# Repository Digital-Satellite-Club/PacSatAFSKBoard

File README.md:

# PacSatAFSKBoard
Hardware design for the PacSat AX5043 based board

This repository contains a board design for use in satellites for
packet message storing and forwarding and for general control.

It has a TMS570LS0914PGE processor for control and packet handling.
It uses 5 AX5043 chips for the radio interfaces, four receive channels
(uplinks) and one transmit channel (downlink).  Operation is full
duplex with receive on 144-148MHz and transmit on 430-440MHz.

Though it is designed for packet satellite, the design can be used for
any sort of full duplex dual band AFSK radio operation with or without
FM.  The AX5043 supports a large number of AFSK protocols (if you can
figure out how to program the AX5043).

With some filter redesign it could support a number of different
bands, too, maybe even up to 1280MHz.

The board also has MRAM storage for persistent data storage and an
RTC for timekeeping.  There's space on the board to add more things.

The board has a CAN interface and a serial interface on top of the
radio interfaces for interfacing to other boards in the system.

Output power is about 2 watts.  It has the ability to measure forward
and reflected power on the output.  It also has a sort of loopback
connector on the RF to test the receive and transmit chain.

The board is designed to be able to be used in an active/standby
configuration where you have two of the same boards and switch the RF
between the boards depending on which is active.

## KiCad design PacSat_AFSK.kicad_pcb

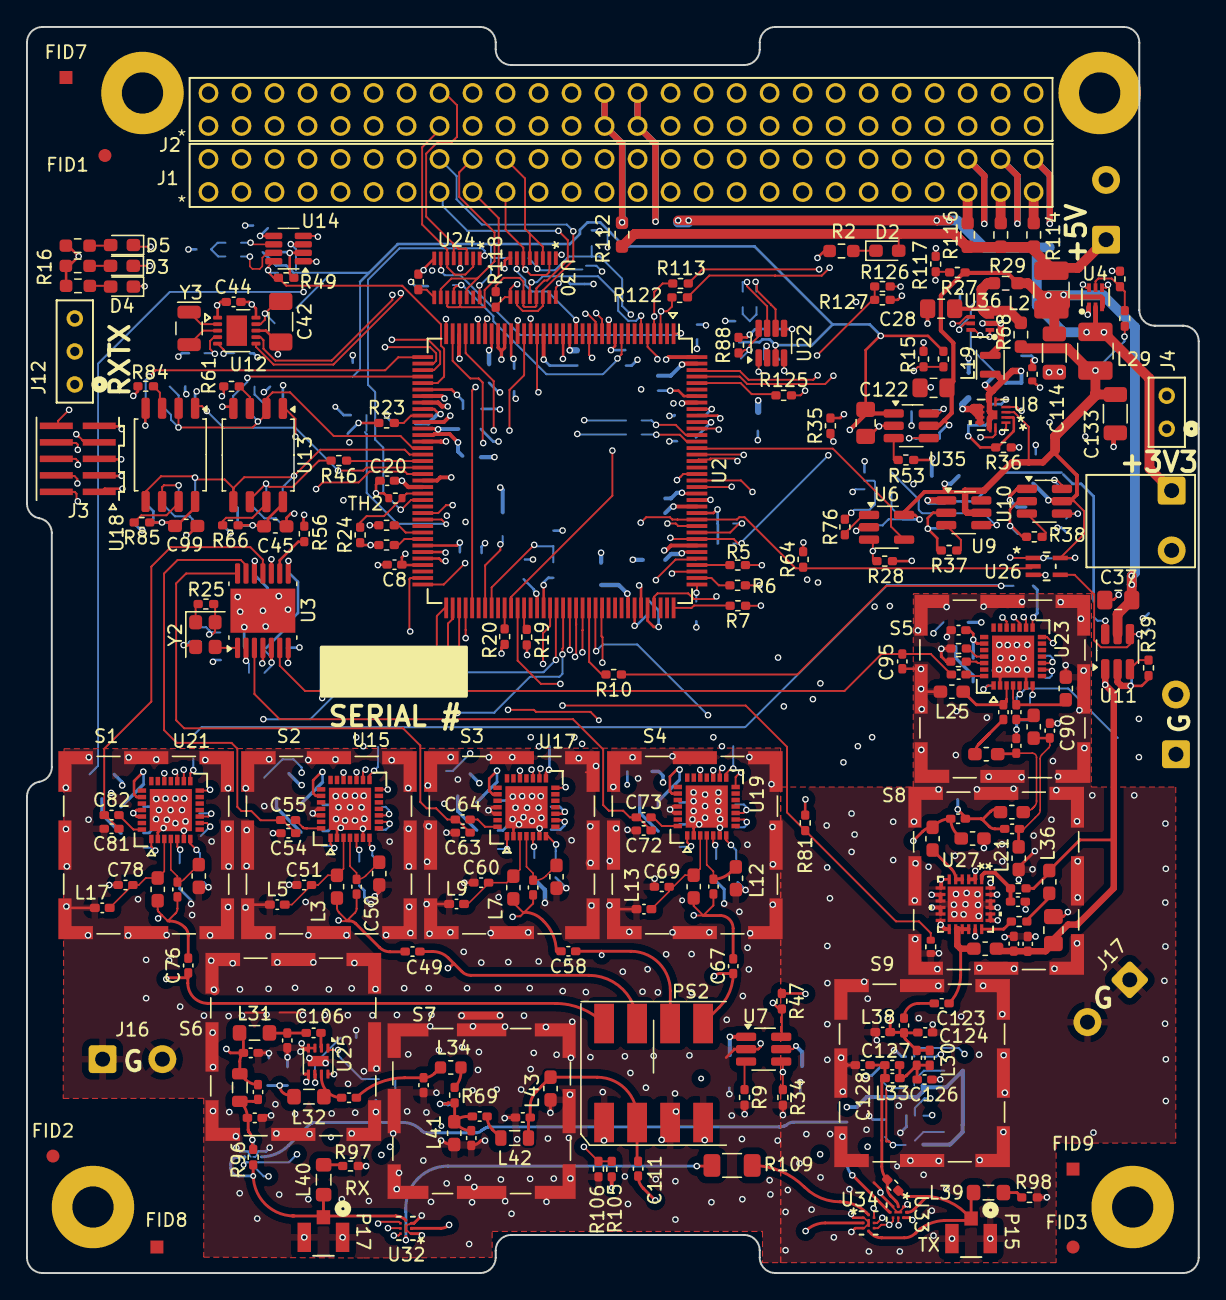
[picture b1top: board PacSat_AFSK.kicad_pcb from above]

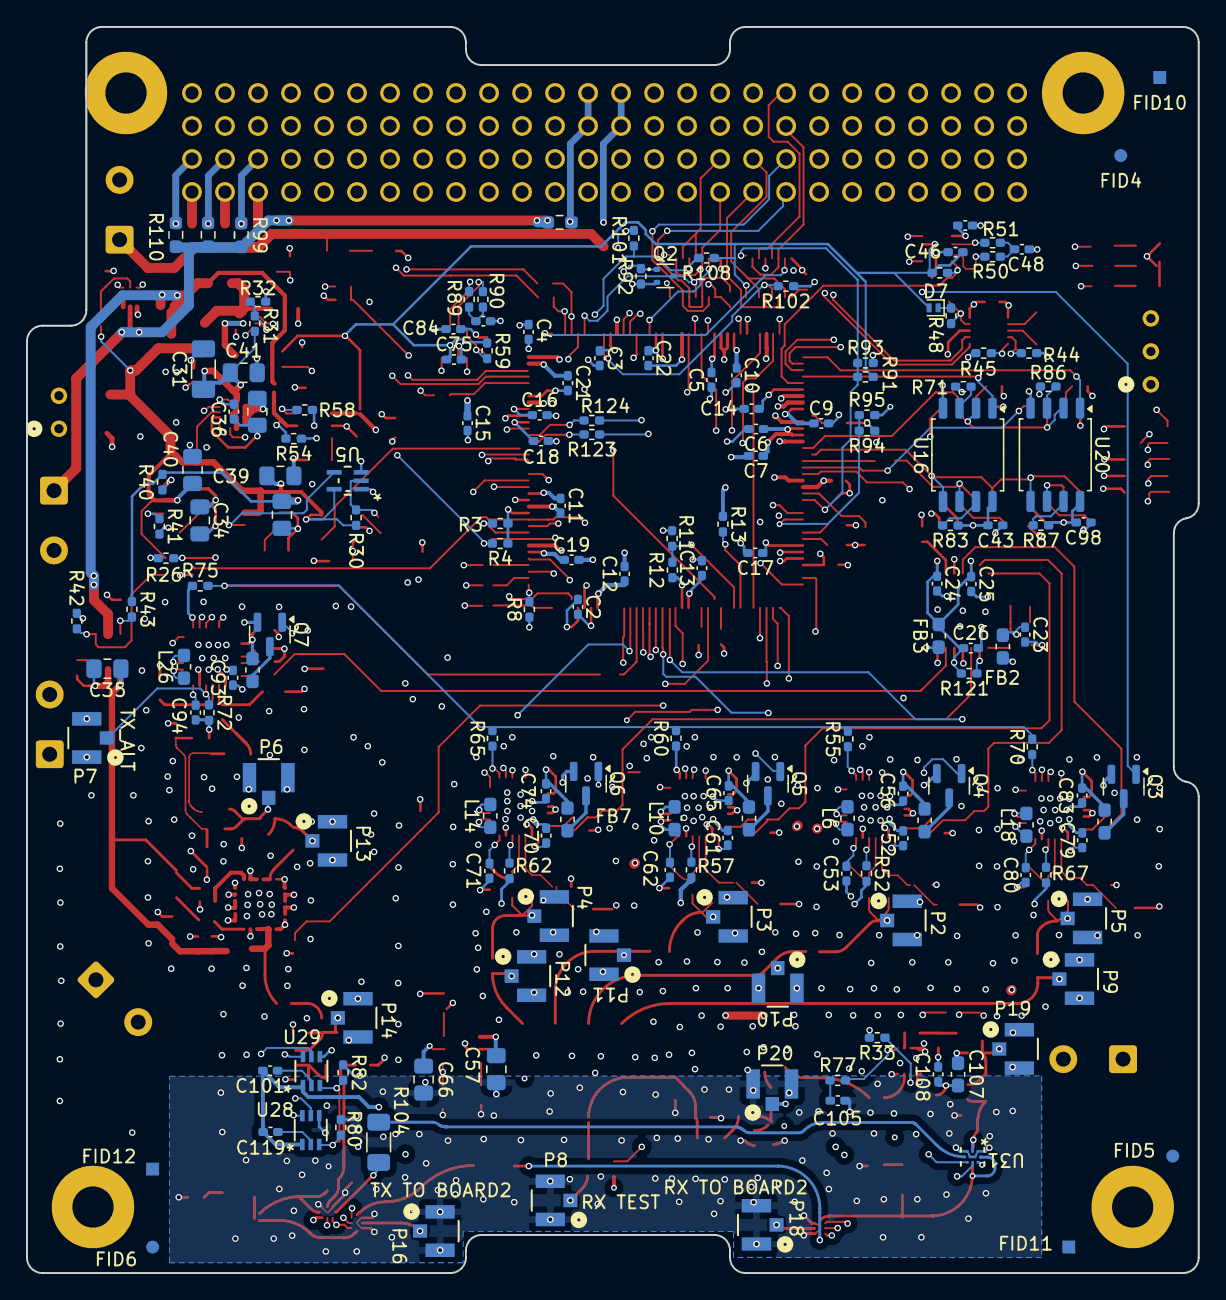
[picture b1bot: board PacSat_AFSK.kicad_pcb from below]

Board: 6 copper layers, 90.2 x 95.9 mm, 405 parts (168 on the bottom side), 283 nets.

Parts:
C2, C3, C4, C5, C6, C7, C8, C9, C10, C11, C12, C13, C14, C15, C16, C17, C18, C19, C20, C21, C22, C23, C24, C25, C26, C43, C44, C46, C47, C75, C84, C98: 100nF; C_0402_1005Metric_Pad0.74x0.62mm_HandSolder
C28: 4.7uF; C_0805_2012Metric_Pad1.18x1.45mm_HandSolder
C31: 22uF; C_1206_3216Metric_Pad1.33x1.80mm_HandSolder
C33, C34, C35, C37, C38, C39, C40, C41, C57, C66, C121, C122: 1uF; C_0805_2012Metric_Pad1.18x1.45mm_HandSolder
C36, C48, C120: 4.7nF; C_0402_1005Metric_Pad0.74x0.62mm_HandSolder
C42: 47uF 10V; C_1206_3216Metric_Pad1.33x1.80mm_HandSolder
C45, C99, C107: 1uF; C_0603_1608Metric_Pad1.08x0.95mm_HandSolder
C49, C58, C67, C76, C105, C108, C113, C115: 100pF; C_0402_1005Metric_Pad0.74x0.62mm_HandSolder
C50, C51, C59, C60, C68, C69, C77, C78: 15pF 1%; C_0402_1005Metric_Pad0.74x0.62mm_HandSolder
C52, C53, C56, C61, C62, C65, C70, C71, C74, C79, C80, C83, C93, C94, C97: 10nF; C_0402_1005Metric_Pad0.74x0.62mm_HandSolder
C54, C63, C72, C81, C95: 6.8pF; C_0402_1005Metric_Pad0.74x0.62mm_HandSolder
C55, C64, C73, C82, C96: 10pF; C_0402_1005Metric_Pad0.74x0.62mm_HandSolder
C88: 5.1pF ±.1; C_0402_1005Metric_Pad0.74x0.62mm_HandSolder
C89, C110: 11pF 1%; C_0402_1005Metric_Pad0.74x0.62mm_HandSolder
C90: 5.6pF ±.1; C_0402_1005Metric_Pad0.74x0.62mm_HandSolder
C91, C92: 4.3pF 1%; C_0402_1005Metric_Pad0.74x0.62mm_HandSolder
C100, C103: 36pF 1%; C_0402_1005Metric_Pad0.74x0.62mm_HandSolder
C101, C106, C109, C111, C112, C116, C119, C123: 1nF; C_0402_1005Metric_Pad0.74x0.62mm_HandSolder
C102: 1pF ±.05; C_0402_1005Metric_Pad0.74x0.62mm_HandSolder
C104, C131: 6.5pF ±.1; C_0402_1005Metric_Pad0.74x0.62mm_HandSolder
C114, C133: 10uF 10V; C_1206_3216Metric
C117: 110pF 1% 30V; C_0402_1005Metric_Pad0.74x0.62mm_HandSolder
C118: 10uF; C_0805_2012Metric_Pad1.18x1.45mm_HandSolder
C124: 7.3pF ±.1 30V; C_0402_1005Metric_Pad0.74x0.62mm_HandSolder
C125: 0.75pF ±.05 30V; C_0402_1005Metric_Pad0.74x0.62mm_HandSolder
C126: 12pF 1% 30V; C_0402_1005Metric_Pad0.74x0.62mm_HandSolder
C127: 2.2pF ±.05 30V; C_0402_1005Metric_Pad0.74x0.62mm_HandSolder
C128: 6.2pF ±.1 30V; C_0402_1005Metric_Pad0.74x0.62mm_HandSolder
C130, C132: 68pF 1%; C_0402_1005Metric_Pad0.74x0.62mm_HandSolder
D2: BLUE LED; LED_0603_1608Metric_Pad1.05x0.95mm_HandSolder
D3: RED LED; LED_0603_1608Metric_Pad1.05x0.95mm_HandSolder
D4: YELLOW LED; LED_0603_1608Metric_Pad1.05x0.95mm_HandSolder
D5: GREEN LED; LED_0603_1608Metric_Pad1.05x0.95mm_HandSolder
D7: RB521CS30L,315; D_SOD-882
FB2, FB3, FB4, FB5, FB6, FB7, FB8: 1KΩ@100MHz; L_0603_1608Metric_Pad1.05x0.95mm_HandSolder
FID1, FID2, FID3, FID4, FID5, FID6: Fiducial (round); Fiducial_1mm_Mask2mm
FID7, FID8, FID9, FID10, FID11, FID12: Fiducial (square); Fiducial_Square_1mm_Mask2mm
H2, H3, H4, H5: CUBESAT_MOUNT_HOLE
J1, J2: ESQ-126-39-G-D; CONN_ESQ-126-39-G-D_SAI
J3: FTSH-105-01-L-DV-K
J4: TS-102-G-A; CON2_1X2_TU_HTS_SAI
J8, J11, J14, J16, J17: Conn_01x02_Pin; SolderWire-0.5sqmm_1x02_P4.6mm_D0.9mm_OD2.1mm
J12: TS-103-G-A; CON3_1X3_TU_HTS_SAI
L2, L29: 3.3uH; L_1210_3225Metric_Pad1.42x2.65mm_HandSolder
L3, L4, L7, L8, L11, L12, L15, L16: 78nH 2%; L_0603_1608Metric_Pad1.05x0.95mm_HandSolder
L5, L9, L13, L17: 1nH; L_0402_1005Metric_Pad0.77x0.64mm_HandSolder
L6, L10, L14, L18, L26: 0; L_0603_1608Metric_Pad1.05x0.95mm_HandSolder
L19: 1uH; L_Murata_DFE201610P
L20, L21: 27nH 2%; L_0603_1608Metric_Pad1.05x0.95mm_HandSolder
L22, L23: 43nH 2%; L_0603_1608Metric_Pad1.05x0.95mm_HandSolder
L24, L25: 100nH; L_0603_1608Metric_Pad1.05x0.95mm_HandSolder
L27: 3.3nH 2%; L_0603_1608Metric_Pad1.05x0.95mm_HandSolder
L28: 43nH 2%; L_0805_2012Metric
L30: 22nH 2%; L_0402_1005Metric_Pad0.77x0.64mm_HandSolder
L31: 91nH 2%; L_0805_2012Metric_Pad1.05x1.20mm_HandSolder
L32: 180nH 2%; L_0805_2012Metric_Pad1.05x1.20mm_HandSolder
L33: 18nH 2%; L_0402_1005Metric_Pad0.77x0.64mm_HandSolder
L34: 47nH 2%; L_0603_1608Metric
L35: 11nH 2%; L_0603_1608Metric_Pad1.05x0.95mm_HandSolder
L36: 68nH; L_0603_1608Metric_Pad1.05x0.95mm_HandSolder
L37: 36nH I>1A; L_0603_1608Metric_Pad1.05x0.95mm_HandSolder
L38: 6.9nH 2%; L_0402_1005Metric_Pad0.77x0.64mm_HandSolder
L39, L40: 470nH; L_0805_2012Metric_Pad1.05x1.20mm_HandSolder
L41, L43: 18nH 2%; L_0603_1608Metric_Pad1.05x0.95mm_HandSolder
L42: 180nH 2%; L_0805_2012Metric
P2, P3, P4, P5, P6, P7, P8, P9, P10, P11, P12, P13, P14, P15, P16, P17, P18, P19, P20: CONUFL001-SMD-T; CONN1_CONUFL_TEC
PS2: AD4PS-1+; CJ725
Q2: BSS138; SOT-523
Q3, Q4, Q5, Q6, Q7: DMP2037U-7; SOT-23
R2: 2.4KΩ; R_0603_1608Metric_Pad0.98x0.95mm_HandSolder
R3, R4, R8, R11, R12, R13, R14, R15, R23, R25, R26, R27, R28, R30, R33, R34, R40, R41, R42, R43, R47, R49, R54, R58, R59, R61, R63, R64, R66, R71, R83, R84, R85, R86, R87, R88, R91, R92, R93, R94, R95, R97, R98, R101, R103, R105, R106, R108, R117, R121: 10KΩ; R_0402_1005Metric_Pad0.72x0.64mm_HandSolder
R5, R6, R7: 22Ω; R_0402_1005Metric_Pad0.72x0.64mm_HandSolder
R9, R38, R53: 143KΩ 1%; R_0402_1005Metric_Pad0.72x0.64mm_HandSolder
R10, R46, R56: 33Ω; R_0402_1005Metric_Pad0.72x0.64mm_HandSolder
R16, R17, R18: 3KΩ; R_0603_1608Metric_Pad0.98x0.95mm_HandSolder
R19, R20, R21, R22: 1KΩ; R_0402_1005Metric_Pad0.72x0.64mm_HandSolder
R24, R35, R81: 10KΩ 1%; R_0402_1005Metric_Pad0.72x0.64mm_HandSolder
R29, R68, R99, R100, R110, R111, R112, R114, R115, R116: 0Ω; R_0603_1608Metric_Pad0.98x0.95mm_HandSolder
R31, R32: 68KΩ 1%; R_0402_1005Metric_Pad0.72x0.64mm_HandSolder
R36: 47KΩ 1%; R_0402_1005Metric_Pad0.72x0.64mm_HandSolder
R37, R39: 45.3KΩ 1%; R_0402_1005Metric_Pad0.72x0.64mm_HandSolder
R44, R45, R48: 4.7KΩ; R_0402_1005Metric_Pad0.72x0.64mm_HandSolder
R50, R51, R89, R90: 61.9Ω; R_0402_1005Metric_Pad0.72x0.64mm_HandSolder
R52, R57, R62, R67, R72, R80, R82: 50Ω; R_0402_1005Metric_Pad0.72x0.64mm_HandSolder
R55, R60, R65, R70, R75: 470Ω; R_0402_1005Metric_Pad0.72x0.64mm_HandSolder
R69, R73, R74, R76, R96, R107, R113, R118, R122, R123, R124, R125, R126, R127: 0Ω; R_0402_1005Metric_Pad0.72x0.64mm_HandSolder
R77: 3.32KΩ 1%; R_0402_1005Metric_Pad0.72x0.64mm_HandSolder
R78: 280Ω; R_0402_1005Metric_Pad0.72x0.64mm_HandSolder
R79: 240Ω; R_0402_1005Metric_Pad0.72x0.64mm_HandSolder
R102: 1MΩ; R_0402_1005Metric_Pad0.72x0.64mm_HandSolder
R104, R109: 50Ω >=2W; R_1206_3216Metric_Pad1.30x1.75mm_HandSolder
R119: 88.7KΩ 1%; R_0402_1005Metric_Pad0.72x0.64mm_HandSolder
R120: 19.6KΩ 1%; R_0402_1005Metric_Pad0.72x0.64mm_HandSolder
S1, S2, S3, S4, S5, S6, S7, S8, S9: 2118714-2; TE_2118714-2
TH2, TH3, TH4: NTCG103JF103FTDS 10KΩ@25C; R_0402_1005Metric
U2: TMS5700914APGEQQ1; TQFP-144_20x20mm_Pitch0.5mm
U3: LMK1C1106A; Texas_HTSSOP-14-1EP_4.4x5mm_P0.65mm_EP3.4x5mm_Mask3.155x3.2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
U4, U36: TPS62A02AQDRLRQ1; DRL0006A-MFG
U5: SN74AHC1G09QDCKRQ1; DCK5
U6: STWD100NYWY3F; SOT-23-5_HandSoldering
U7, U9, U10, U11, U35: MAX4995AAUT+T; SOT-23-6_Handsoldering
U8: MP5073GG-P; QFN-12_MP5073_MNP
U12: MAX31331TETB+; TDFN-10-1EP_3x3mm_P0.5mm_EP0.9x2mm
U13, U16, U18, U20: AS1016204-0108X0PSAY; SOIC-8_5.3x5.3mm_P1.27mm
U14, U22: TCAN1044ADDFRQ1; TSOT-23-8
U15, U17, U19, U21, U23: AX5043; QFN28
U24, U30: SN3257QDYYRQ1; DYY0016A
U25: QPL9547; DFN-8-1EP_2x2mm_P0.5mm_EP0.8x1.6mm
U26: SN74AHC1G02QDCKRQ1; DCK5
U27: TQP7M9106; QFN24_TQP7M9104_QOR
U28, U29: ADL5501AKSZ-R7; KS-6_ADI
U31, U32, U33, U34: QPC1022TR7; QPC1022_QOR
Y2: O 16,0-JT22CT-A-P-3,3-LF; Oscillator_SMD_SiT_PQFN-4Pin_2.5x2.0mm
Y3: 32.768kHz; Crystal_SMD_EuroQuartz_EQ161-2Pin_3.2x1.5mm

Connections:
3.3V_IN: J14.1, L29.1, R99.2, R100.2, R110.2, R111.2, U4.2 (SW)
5V_IN: D2.2 (A), J11.1, L2.2, R112.1, R114.1, R115.1, R116.1
+1.2V: C6.1, C7.1, C9.1, C10.1, C11.1, C12.1, C13.1, C15.1, C19.1, C20.1, C21.1, C22.1, C38.1, R13.1, U2.17 (VCC), U2.29 (VCC), U2.45 (VCC), U2.48 (VCC), U2.49 (VCC), U2.57 (VCC), U2.87 (VCC), U2.101 (VCC), U2.114 (VCC), U2.123 (VCC), U2.137 (VCC), U2.143 (VCC), U8.7 (NC), U8.8 (NC), U8.9 (VOUT), U8.10 (NC)
+3.3V: C2.1, C3.1, C4.1, C5.1, C8.1, C14.1, C16.1, C17.1, C18.1, C33.1, C43.1, C44.1, C45.1, C47.1, C84.1, C98.1, C99.1, C101.2, C119.2, FB2.1, FB3.1, J3.1, R3.1, R4.1, R8.1, R11.1, R16.1, R17.1, R18.1, R21.1, R23.1, R24.1, R35.1, R40.1, R43.1, R47.1, R58.1, R61.2, R66.1, R71.2, R81.1, R83.1, R84.2, R85.1, R86.2, R87.1, R94.1, R102.1, U2.10 (VCCIO), U2.26 (VCCIO), U2.42 (VCCIO), U2.66 (ADREFHI), U2.69 (VCCAD), U2.104 (VCCIO), U2.120 (VCCIO), U2.134 (VCCP), U2.136 (VCCIO), U9.1 (OUT), U12.10 (VCC), U13.8 (VCC), U14.5 (NC/VIO), U16.8 (VCC), U18.8 (VCC), U20.8 (VCC), U22.5 (NC/VIO), U28.1 (VPOS), U29.1 (VPOS)
+5V: C37.1, C114.1, C122.1, L2.1, R27.2, R29.1, R54.2, U4.3 (VIN), U11.5 (IN), U35.5 (IN)
+5VAL: C46.1, C66.1, C75.1, C121.1, D7.2 (A), R14.1, R59.1, R63.1, R91.1, R105.1, R108.1, U7.5 (IN), U14.3 (VCC), U22.3 (VCC), U24.16 (VDD), U30.16 (VDD), U31.7 (VDD), U32.7 (VDD), U33.7 (VDD), U34.7 (VDD), U35.1 (OUT)
/AX5043/RX_1_ax5043/RXANT_N: C77.1, L16.2, U21.4 (ANTN)
/AX5043/RX_1_ax5043/RXANT_P: C78.2, L15.2, L17.2, U21.3 (ANTP)
/AX5043/RX_2_ax5043/RX2ANT_N: C50.1, L4.2, U15.4 (ANTN)
/AX5043/RX_2_ax5043/RX2ANT_P: C51.2, L3.2, L5.2, U15.3 (ANTP)
/AX5043/RX_3_ax5043/RX3_N: C59.1, L8.2, U17.4 (ANTN)
/AX5043/RX_3_ax5043/RX3_P: C60.2, L7.2, L9.2, U17.3 (ANTP)
/AX5043/RX_4_ax5043/RX4ANT_N: C68.1, L12.2, U19.4 (ANTN)
/AX5043/RX_4_ax5043/RX4ANT_P: C69.2, L11.2, L13.2, U19.3 (ANTP)
/AX5043/TX_ax5043/TXANT_N: C92.1, L24.2, U23.4 (ANTN)
/AX5043/TX_ax5043/TXANT_P: C91.1, L25.2, U23.3 (ANTP)
/AX5043/TX_ax5043/TXa_N: C92.2, L23.2
/AX5043/TX_ax5043/TXa_P: C91.2, L22.2
/AX5043/TX_ax5043/TXb_N: C88.1, C90.1, L21.1, L23.1
/AX5043/TX_ax5043/TXb_P: C89.1, L20.2, L22.1
/PC104_IO/3V3_S1: J1.48, R99.1
/PC104_IO/3V3_S2: J1.50, R100.1
/PC104_IO/3V3_S3: J1.52, R110.1
/PC104_IO/3V3_p: J2.27, J2.28, R111.1
/PC104_IO/5V_S1: J1.47, R116.2
/PC104_IO/5V_S2: J1.49, R115.2
/PC104_IO/5V_S3: J1.51, R114.2
/PC104_IO/5V_p: J2.25, J2.26, R112.2
/PC104_IO/VBATT_p: J2.45, J2.46, R126.1
/Power/1.2V_INPUT: C28.1, R29.2, R68.2, U36.3 (VIN)
/Power/PA_POWER_ON: R42.1, U11.4 (ON), U26.4 (Y)
/Power/WATCHDOG_OUT_N: R30.2, R76.1, U5.2 (B)
/Rx_Power_Divider/S+: C111.2, C132.2, L42.1, L43.1, PS2.2 (S1)
ACTIVE1_N: J1.19, U30.2 (S1A), U30.6 (S2B), U31.5 (CTRL), U32.5 (CTRL), U33.5 (CTRL), U34.5 (CTRL)
ACTIVE2_N: J1.20, U30.3 (S1B), U30.5 (S2A)
ACTIVE_N: R101.1, R108.2, U2.133 (GIOB_1), U30.4 (D1)
AX5043 PWR EN: R41.1, U2.141 (N2HET1_20), U10.4 (ON)
AX5043_3V3: C34.1, Q3.2 (S), Q4.2 (S), Q5.2 (S), Q6.2 (S), Q7.2 (S), U10.1 (OUT)
AX5043_CLK: R10.1, R55.2, R60.2, R65.2, R70.2, R75.2
AX5043_EN_RX1_N: Q3.1 (G), U2.36 (N2HET1_4)
AX5043_EN_RX2_N: Q4.1 (G), U2.35 (N2HET1_9)
AX5043_EN_RX3_N: Q5.1 (G), U2.33 (N2HET1_7)
AX5043_EN_RX4_N: Q6.1 (G), U2.24 (N2HET1_3)
AX5043_EN_TX_N: Q7.1 (G), U2.89 (CAN1TX)
AX5043_IRQ_RX1: U2.5 (GIOA_1), U21.19 (IRQ)
AX5043_IRQ_RX2: U2.126 (GOIB_0), U15.19 (IRQ)
AX5043_IRQ_RX3: U2.22 (GIOA_7), U17.19 (IRQ)
AX5043_IRQ_RX4: U2.14 (GIOA_5), U19.19 (IRQ)
AX5043_IRQ_TX: U2.142 (GIOB_2), U23.19 (IRQ)
AX5043_MISO: U2.94 (MIBSPI1SOMI), U15.16 (MISO), U17.16 (MISO), U19.16 (MISO), U21.16 (MISO), U23.16 (MISO)
AX5043_MOSI: U2.93 (MIBSPI1SIMO), U15.17 (MOSI), U17.17 (MOSI), U19.17 (MOSI), U21.17 (MOSI), U23.17 (MOSI)
AX5043_SEL1_N: U2.90 (CAN1RX), U21.14 (SEL)
AX5043_SEL2_N: U2.91 (N2HET1_24), U15.14 (SEL)
AX5043_SEL3_N: U2.92 (N2HET1_26), U17.14 (SEL)
AX5043_SEL4_N: U2.96 (MIBSPI1NENA), U19.14 (SEL)
AX5043_SEL_TX_N: U2.97 (MIBSPI5NENA), U23.14 (SEL)
BOARD1_RF_BYPASS: R104.2, U31.4 (RF1)
BOARD2_RF_BYPASS: R109.2, U32.8 (RF2)
BOARD_NUM: R91.2, R93.1, U2.59 (AD1IN_17), U24.1 (SEL), U30.1 (SEL)
CANA+: J1.23, R50.1, U14.7 (CA_NH)
CANA-: J1.24, R51.2, U14.6 (CA_NL)
CANB+: J1.33, R89.1, U22.7 (CA_NH)
CANB-: J1.34, R90.2, U22.6 (CA_NL)
CAN_A_EN_N: R49.1, R63.2, U2.41 (N2HET1_15), U14.8 (STB)
CAN_A_RX: U2.12 (CAN3RX), U14.4 (RX_D)
CAN_A_TX: U2.13 (CAN3TX), U14.1 (TXD)
CAN_B_EN_N: R59.2, R88.1, U2.105 (MIBSPI1NCS_0), U22.8 (STB)
CAN_B_RX: U2.129 (CAN2RX), U22.4 (RX_D)
CAN_B_TX: U2.128 (CAN2TX), U22.1 (TXD)
Clock_CPU: R56.2, U2.18 (OSCIN)
Clock_RX1: C81.1, C82.1, U3.11 (Y2)
Clock_RX2: C54.1, C55.1, U3.13 (Y3)
Clock_RX3: C63.1, C64.1, U3.14 (Y1)
Clock_RX4: C72.1, C73.1, U3.3 (YO)
Clock_TX: C95.2, C96.1, U3.6 (Y4)
EXTERN_CONTROL: R94.2, R95.1, U2.62 (AD1IN_18)
FAULT1_N: J2.15, U24.2 (S1A), U24.6 (S2B)
FAULT2_N: J2.16, U24.3 (S1B), U24.5 (S2A)
FAULT_N: R3.2, U2.117 (nERROR), U24.4 (D1)
FEED_WATCHDOG: U2.130 (MIBSPI1NCS_1), U6.4 (WDI)
FWD_PWR: U2.74 (AD1IN_3), U29.6 (VRMS)
GND: C2.2, C3.2, C4.2, C5.2, C6.2, C7.2, C8.2, C9.2, C10.2, C11.2, C12.2, C13.2, C14.2, C15.2, C16.2, C17.2, C18.2, C19.2, C20.2, C21.2, C22.2, C23.2, C24.2, C25.2, C26.2, C28.2, C31.2, C33.2, C34.2, C35.2, C36.2, C37.2, C38.2, C39.1, C40.2, C41.2, C42.2, C43.2, C44.2, C45.2, C46.2, C47.2, C48.2, C51.1, C52.2, C53.2, C54.2, C56.2, C57.2, C60.1, C61.2, C62.2, C63.2, C65.2, C66.2, C69.1, C70.2, C71.2, C72.2, C74.2, C75.2, C78.1, C79.2, C80.1, C81.2, C83.2, C84.2, C89.2, C90.2, C93.2, C94.2, C95.1, C97.2, C98.2, C99.2, C100.1, C103.1, C104.2, C105.2, C107.1, C108.1, C110.1, C113.2, C114.2, C115.2, C116.2, C118.2, C120.2, C121.2, C122.2, C124.1, C126.1, C128.1, C130.1, C132.1, C133.2, H2.1, H3.1, H4.1, H5.1, J2.29, J2.30, J2.32, J3.3, J3.5, J3.9, J8.1, J8.2, J11.2, J12.3 (GND), J14.2, J16.1, J16.2, J17.1, J17.2, L4.1, L5.1, L8.1, L9.1, L12.1, L13.1, L16.1, L17.1, L21.2, L24.1, L25.1, L27.1, L38.1, L41.2, L43.2, P2.2, P2.3, P3.2, P3.3, P4.2, P4.3, P5.2, P5.3, P6.2, P6.3, P7.2, P7.3, P8.2, P8.3, P9.2, P9.3, P10.2, P10.3, P11.2, P11.3, P12.2, P12.3, P13.2, P13.3, P14.2, P14.3, P15.2, P15.3, P16.2, P16.3, P17.2, P17.3, P18.2, P18.3, P19.2, P19.3, P20.2, P20.3, PS2.1 (GND), PS2.3 (GND), PS2.4 (GND), Q2.2 (S), R2.2, R9.2, R12.2, R15.2, R19.1, R20.1, R22.1, R28.2, R32.1, R33.2, R34.2, R36.2, R37.2, R38.2, R39.2, R41.2, R42.2, R44.1, R45.1, R49.2, R52.2, R53.2, R57.2, R62.2, R64.2, R67.2, R72.2, R73.2, R74.2, R80.2, R82.2, R88.2, R92.2, R93.2, R95.2, R97.2, R98.2, R101.2, R103.2, R106.2, R117.1, R120.1, R127.2, S1.SH1 (SHIELD), S1.SH2 (SHIELD__1), S1.SH3 (SHIELD__2), S1.SH4 (SHIELD__3), S1.SH5 (SHIELD__4), S1.SH6 (SHIELD__5), S1.SH7 (SHIELD__6), S1.SH8 (SHIELD__7), S2.SH1 (SHIELD), S2.SH2 (SHIELD__1), S2.SH3 (SHIELD__2), S2.SH4 (SHIELD__3), S2.SH5 (SHIELD__4), S2.SH6 (SHIELD__5), S2.SH7 (SHIELD__6), S2.SH8 (SHIELD__7), S3.SH1 (SHIELD), S3.SH2 (SHIELD__1), S3.SH3 (SHIELD__2), S3.SH4 (SHIELD__3), S3.SH5 (SHIELD__4), S3.SH6 (SHIELD__5), S3.SH7 (SHIELD__6), S3.SH8 (SHIELD__7), S4.SH1 (SHIELD), S4.SH2 (SHIELD__1), S4.SH3 (SHIELD__2), S4.SH4 (SHIELD__3), S4.SH5 (SHIELD__4), S4.SH6 (SHIELD__5), S4.SH7 (SHIELD__6), S4.SH8 (SHIELD__7), S5.SH1 (SHIELD), S5.SH2 (SHIELD__1), S5.SH3 (SHIELD__2), S5.SH4 (SHIELD__3), S5.SH5 (SHIELD__4), S5.SH6 (SHIELD__5), S5.SH7 (SHIELD__6), S5.SH8 (SHIELD__7), S6.SH1 (SHIELD), S6.SH2 (SHIELD__1), S6.SH3 (SHIELD__2), S6.SH4 (SHIELD__3), S6.SH5 (SHIELD__4), S6.SH6 (SHIELD__5), S6.SH7 (SHIELD__6), S6.SH8 (SHIELD__7), S7.SH1 (SHIELD), S7.SH2 (SHIELD__1), S7.SH3 (SHIELD__2), S7.SH4 (SHIELD__3), S7.SH5 (SHIELD__4), S7.SH6 (SHIELD__5), S7.SH7 (SHIELD__6), S7.SH8 (SHIELD__7), S8.SH1 (SHIELD), S8.SH2 (SHIELD__1), S8.SH3 (SHIELD__2), S8.SH4 (SHIELD__3), S8.SH5 (SHIELD__4), S8.SH6 (SHIELD__5), S8.SH7 (SHIELD__6), S8.SH8 (SHIELD__7), S9.SH1 (SHIELD), S9.SH2 (SHIELD__1), S9.SH3 (SHIELD__2), S9.SH4 (SHIELD__3), S9.SH5 (SHIELD__4), S9.SH6 (SHIELD__5), S9.SH7 (SHIELD__6), S9.SH8 (SHIELD__7), TH2.2, TH3.2, TH4.2, U2.11 (VSS), U2.21 (VSS), U2.27 (VSS), U2.28 (VSS), U2.34 (TEST), U2.43 (VSS), U2.44 (VSS), U2.47 (VSS), U2.50 (VSS), U2.56 (VSS), U2.67 (ADREFLO), U2.68 (VSSAD), U2.88 (VSS), U2.102 (VSS), U2.103 (VSS), U2.115 (VSS), U2.121 (VSS), U2.122 (VSS), U2.135 (VSS), U2.138 (VSS), U2.144 (VSS), U3.4 (GND), U3.7 (GND), U3.10 (GND), U3.15 (PAD), U4.1 (GND), U5.3 (GND), U6.2 (GND), U7.2 (GND), U8.2 (GND), U9.2 (GND), U10.2 (GND), U11.2 (GND), U12.1 (GND), U12.8 (DIN), U13.4 (GND), U14.2 (GND), U15.0 (GND), U15.2 (GND), U15.6 (GND), U15.25 (GPADC1), U15.26 (GPADC2), U16.4 (GND), U17.0 (GND), U17.2 (GND), U17.6 (GND), U17.25 (GPADC1), U17.26 (GPADC2), U18.4 (GND), U19.0 (GND), U19.2 (GND), U19.6 (GND), U19.25 (GPADC1), U19.26 (GPADC2), U20.4 (GND), U21.0 (GND), U21.2 (GND), U21.6 (GND), U21.25 (GPADC1), U21.26 (GPADC2), U22.2 (GND), U23.0 (GND), U23.2 (GND), U23.6 (GND), U24.8 (GND), U25.3 (GND), U25.4 (GND), U25.5 (GND), U25.8 (GND), U25.9 (GND), U26.3 (GND), U27.2 (GND), U27.3 (GND), U27.6 (GND), U27.7 (GND), U27.8 (GND), U27.9 (GND), U27.10 (GND), U27.11 (GND), U27.12 (GND), U27.13 (GND), U27.17 (GND), U27.19 (GND), U27.20 (GND), U27.21 (GND), U27.22 (GND), U27.23 (GND), U27.24 (GND), U27.25 (RF/DC-GND), U28.4 (COMM), U29.4 (COMM), U30.8 (GND), U31.1 (GND), U31.3 (GND), U31.9 (GND), U32.1 (GND), U32.3 (GND), U32.9 (GND), U33.1 (GND), U33.3 (GND), U33.9 (GND), U34.1 (GND), U34.3 (GND), U34.9 (GND), U35.2 (GND), U36.1 (GND), Y2.2 (GND)
HW_POWER_OFF1_N: J1.15, R118.1, U30.11 (S3A), U30.13 (S4B)
HW_POWER_OFF2_N: J1.16, U30.10 (S3B), U30.14 (S4A)
HW_POWER_OFF_N: R27.1, R117.2, R118.2, U4.4 (EN), U5.1 (A), U30.9 (D3), U36.4 (EN)
I2C_SCL: R122.2, U2.3 (MIBSPI3NCS_3), U12.6 (SCL)
I2C_SDA: R113.2, U2.4 (MIBSPI3NCS_2), U12.7 (SDA)
LNA_ENABLE: R34.1, U2.31 (N2HET1_5), U7.4 (ON)
LNA_VCC: C57.1, C107.2, C108.2, L32.1, U7.1 (OUT)
MRAM_CLK: R46.1, U2.53 (MIBSPI3CLK)
MRAM_MISO: U2.51 (MIBSPI3SOMI), U13.2 (SO/IO1), U16.2 (SO/IO1), U18.2 (SO/IO1), U20.2 (SO/IO1)
MRAM_MOSI: U2.52 (MIBSPI3SIMO), U13.5 (SI/IO0), U16.5 (SI/IO0), U18.5 (SI/IO0), U20.5 (SI/IO0)
MRAM_NCS0: U2.55 (MIBSPI3NCS_0), U13.1 (CS)
MRAM_NCS1: U2.54 (MIBSPI3NENA), U18.1 (CS)
MRAM_NCS2: U2.40 (MIBSPI1NCS_2), U16.1 (CS)
MRAM_NCS3: U2.37 (MIBSPI3NCS_1), U20.1 (CS)
unnamed: C24.1, C25.1, C26.1, FB3.2, R121.1, U3.5 (Vdd), U3.8 (Vdd), U3.12 (Vdd)
unnamed: C48.1, R50.2, R51.1
unnamed: C52.1, U15.1 (VDD_ANA)
unnamed: C53.1, U15.7 (VDD_ANA)
unnamed: C61.1, U17.1 (VDD_ANA)
unnamed: C62.1, U17.7 (VDD_ANA)
unnamed: C70.1, U19.1 (VDD_ANA)
unnamed: C71.1, U19.7 (VDD_ANA)
unnamed: C79.1, U21.1 (VDD_ANA)
unnamed: C80.2, U21.7 (VDD_ANA)
unnamed: C93.1, U23.1 (VDD_ANA)
unnamed: C94.1, U23.7 (VDD_ANA)
unnamed: C104.1, C106.2, L31.1
unnamed: C105.1, R77.1
unnamed: C106.1, U25.2
unnamed: C109.1, C110.2, L34.2
unnamed: C109.2, L32.2, U25.7
unnamed: C117.2, C123.2
unnamed: C120.1, R89.2, R90.1
unnamed: C123.1, L37.1, U27.14 (RFOUT/VCC), U27.15 (RFOUT/VCC), U27.16 (RFOUT/VCC)
unnamed: C125.2, C126.2, C127.1, L30.2, L33.1
unnamed: C131.1, L42.2
unnamed: D2.1 (K), R2.1
unnamed: D3.2 (A), R16.2
unnamed: D3.1 (K), U2.25 (N2HET1_0)
unnamed: D4.2 (A), R17.2
unnamed: D4.1 (K), U2.23 (N2HET1_1)
unnamed: D5.2 (A), R18.2
unnamed: D5.1 (K), U2.30 (N2HET1_2)
unnamed: D7.1 (K), R48.2
unnamed: J1.41, R113.1
unnamed: J1.43, R122.1
unnamed: J2.21, R123.1
unnamed: J2.22, R124.2
unnamed: J2.50, R125.2
unnamed: J3.2, R7.1
unnamed: J3.4, R5.1
unnamed: J3.6, U2.111 (TDO)
unnamed: J3.7, U2.113 (RTCK)
unnamed: J3.8, R6.1
unnamed: J12.1 (RX), U2.38 (N2HET1_6)
unnamed: J12.2 (TX), U2.39 (N2HET1_13)
unnamed: L34.1, R69.1
unnamed: L35.2, U27.4 (RFIN), U27.5 (RFIN)
unnamed: L36.1, R79.1
unnamed: L39.2, R98.1
unnamed: L40.2, R97.1
unnamed: C49.2, C50.2, L3.1, P2.1 (In)
unnamed: C58.2, C59.2, L7.1, P3.1 (In)
unnamed: C67.2, C68.2, L11.1, P4.1 (In)
unnamed: C76.2, C77.2, L15.1, P5.1 (In)
unnamed: P7.1 (In), R72.1, U23.5 (ANTP1)
unnamed: C111.1, P8.1 (In)
unnamed: C112.2, L27.2, L35.1, P13.1 (In)
unnamed: C117.1, C124.2, C125.1, L30.1, L38.2, P14.1 (In)
unnamed: L39.1, P15.1 (In), R107.1, U33.8 (RF2), U34.4 (RF1)
unnamed: P16.1 (In), U34.2 (ANT)
unnamed: L40.1, P17.1 (In), R96.1, U31.8 (RF2), U32.4 (RF1)
unnamed: P18.1 (In), U32.2 (ANT)
unnamed: C102.1, C103.2, L28.1, L31.2, P19.1 (In)
unnamed: C130.2, C131.2, L41.1, P20.1 (In), R69.2
unnamed: FB4.2, Q3.3 (D)
unnamed: FB5.2, Q4.3 (D)
unnamed: FB6.2, Q5.3 (D)
unnamed: FB7.2, Q6.3 (D)
unnamed: FB8.2, Q7.3 (D)
unnamed: R11.2, R12.1, U2.80 (AD1IN_6)
unnamed: R14.2, R15.1, U2.77 (AD1IN_12)
unnamed: R13.2, U2.79 (AD1IN_13)
unnamed: R24.2, TH2.1, U2.58 (AD1IN_16)
unnamed: R10.2, U2.95 (MIBSPI1CLK)
unnamed: R5.2, U2.112 (TCK)
unnamed: R6.2, U2.110 (TDI)
unnamed: R7.2, U2.108 (TMS)
unnamed: R23.2, U2.46 (nPORRST)
unnamed: R8.2, U2.109 (nTRST)
unnamed: R121.2, U3.2 (1G)
unnamed: U3.1 (CLKIN), Y2.3 (OUT)
unnamed: R56.1, U3.9 (Y5)
unnamed: R119.1, R120.2, U4.5 (FB)
unnamed: J4.1, R28.1, U6.3 (EN_N)
unnamed: R76.2, U6.1 (WDO_N)
unnamed: R9.1, U7.3 (SETI)
unnamed: R36.1, U8.4 (ILIM)
unnamed: C36.1, U8.5 (SS)
unnamed: R37.1, U9.3 (SETI)
unnamed: R38.1, U10.3 (SETI)
unnamed: R39.1, U11.3 (SETI)
unnamed: R44.2, U12.4 (INTA_N)
unnamed: R45.2, U12.5 (INTB_N)
unnamed: C42.1, R48.1, U12.9 (Vbat)
unnamed: U12.3 (X1), Y3.2
unnamed: U12.2 (X2), Y3.1
unnamed: R66.2, U13.7 (RST/IO3)
unnamed: R46.2, U13.6 (SCK), U16.6 (SCK), U18.6 (SCK), U20.6 (SCK)
unnamed: R61.1, U13.3 (WP#/IO2)
unnamed: R52.1, U15.5 (ANTP1)
unnamed: C55.2, U15.28 (CLK16P)
unnamed: R55.1, U15.15 (CLK)
unnamed: L6.2, U15.10 (L1)
unnamed: L6.1, U15.9 (L2)
unnamed: C56.1, FB5.1, U15.23 (VDD_IO)
unnamed: R83.2, U16.7 (RST/IO3)
unnamed: R71.1, U16.3 (WP#/IO2)
unnamed: R57.1, U17.5 (ANTP1)
unnamed: C64.2, U17.28 (CLK16P)
unnamed: R60.1, U17.15 (CLK)
unnamed: L10.2, U17.10 (L1)
unnamed: L10.1, U17.9 (L2)
unnamed: C65.1, FB6.1, U17.23 (VDD_IO)
unnamed: R85.2, U18.7 (RST/IO3)
unnamed: R84.1, U18.3 (WP#/IO2)
unnamed: R62.1, U19.5 (ANTP1)
unnamed: C73.2, U19.28 (CLK16P)
unnamed: R65.1, U19.15 (CLK)
unnamed: L14.2, U19.10 (L1)
unnamed: L14.1, U19.9 (L2)
unnamed: C74.1, FB7.1, U19.23 (VDD_IO)
unnamed: R87.2, U20.7 (RST/IO3)
unnamed: R86.1, U20.3 (WP#/IO2)
unnamed: R67.1, U21.5 (ANTP1)
unnamed: C82.2, U21.28 (CLK16P)
unnamed: R70.1, U21.15 (CLK)
unnamed: L18.2, U21.10 (L1)
unnamed: L18.1, U21.9 (L2)
unnamed: C83.1, FB4.1, U21.23 (VDD_IO)
unnamed: C96.2, U23.28 (CLK16P)
unnamed: R75.1, U23.15 (CLK)
unnamed: R73.1, U23.25 (GPADC1)
unnamed: R74.1, U23.26 (GPADC2)
unnamed: L26.2, U23.10 (L1)
unnamed: L26.1, U23.9 (L2)
unnamed: C97.1, FB8.1, U23.23 (VDD_IO)
unnamed: R103.1, U24.9 (D3)
unnamed: R77.2, U25.1 (Vb)
unnamed: R33.1, U25.6 (~EN)
unnamed: R79.2, U27.18 (IREF)
unnamed: C113.1, R78.2, U27.1 (VBIAS)
unnamed: C119.1, U28.2 (FLTR)
unnamed: R80.1, R82.1, U28.3 (RFIN), U29.3 (RFIN)
unnamed: C101.1, U29.2 (FLTR)
unnamed: R104.1, U33.4 (RF1)
unnamed: R109.1, U34.8 (RF2)
unnamed: R54.1, U35.4 (ON)
unnamed: R53.1, U35.3 (SETI)
unnamed: R31.1, R32.2, U36.5 (FB)
unnamed: L19.2, U36.2 (SW)
unnamed: R25.2, Y2.1 (VC)
unnamed: C23.1, FB2.2, R25.1, Y2.4 (VDD)
OTHER_ACTIVE_N: U2.16 (GIOA_6), U30.7 (D2)
OTHER_FAULT_N: U2.1 (GIOB_3), U24.7 (D2)
OTHER_HW_POWER_OFF: Q2.1 (G), R92.1, U2.118 (N2HET1_10)
OTHER_HW_POWER_OFF_N: Q2.3 (D), U2.6 (N2HET1_11), U30.12 (D4)
OTHER_PRESENCE_N: R102.2, U2.9 (GIOA_2), U24.12 (D4)
PA_PWR_EN_N: R26.2, U2.125 (N2HET1_14), U26.1 (A)
PA_TEMP: R81.2, TH4.1, U2.84 (AD1IN_23)
PC104_ABF0: R125.1, U2.140 (N2HET1_18)
PC104_RX: R123.2, U2.131 (LINRX)
PC104_TX: R124.1, U2.132 (LINTX)
POWER_ENABLE: U5.4 (Y), U8.1 (EN), U9.4 (ON)
POWER_TEMP: R35.2, TH3.1, U2.83 (AD1IN_8)
POW_MEAS_EN: U2.124 (N2HET1_12), U28.5 (ENBL), U29.5 (ENBL)
PRESENCE1_N: J1.17, U24.11 (S3A), U24.13 (S4B)
PRESENCE2_N: J1.18, U24.10 (S3B), U24.14 (S4A)
PWR_FLAG_5VAL: R58.2, U2.72 (AD1IN_10), U35.6 (~FLAG)
PWR_FLAG_AX5043: R40.2, U2.61 (AD1IN_7), U10.6 (~FLAG)
PWR_FLAG_LNA: R47.2, U2.75 (AD1IN_11), U7.6 (~FLAG)
PWR_FLAG_SSPA: R43.2, U2.76 (AD1IN_4), U11.6 (~FLAG)
Port1_P: C76.1, P9.1 (In), PS2.8 (Port1)
Port2_P: C49.1, P10.1 (In), PS2.7 (Port2)
Port3_P: C58.1, P11.1 (In), PS2.6 (Port3)
Port4_P: C67.1, P12.1 (In), PS2.5 (Port4)
Processor_Reset: J3.10, R4.2, U2.116 (nRST), U4.6 (PG), U8.12 (PG), U36.6 (PG)
REG_1V2: C31.1, C41.1, L19.1, R31.2, U8.6 (VIN), U8.11 (VIN), U8.13 (VIN)
REG_3V3: C39.2, C40.1, C133.1, J4.2, L29.2, R26.1, R30.1, R68.1, R119.2, U5.5 (VCC), U6.5 (VCC), U8.3 (VCC), U9.5 (IN), U10.5 (IN), U26.5 (VCC)
REV_PWR: U2.73 (AD1IN_2), U28.6 (VRMS)
RF_IN_SWITCH: C100.2, C102.2, L28.2, R96.2, U31.2 (ANT)
RF_OUT_SWITCH: C127.2, C128.2, L33.2, R107.2, U33.2 (ANT)
RF_SWITCH_EN: R105.2, R106.1, U31.6 (EN), U32.6 (EN), U33.6 (EN), U34.6 (EN)
SSPA_VCC: C35.1, C115.1, C116.1, C118.1, L36.2, L37.2, R78.1, U11.1 (OUT)
TX_OUT_DRV: C88.2, C112.1, L20.1, P6.1 (In)
UMBILICAL_ATTACHED: J2.18, R64.1, U2.119 (ECLK), U26.2 (B)
VBATT: R126.2, R127.1, U2.71 (AD1IN_1)
VER_BIT0: R22.2, U2.64 (AD1IN_20)
VER_BIT1: R21.2, U2.65 (AD1IN_21)
VER_BIT2: R20.2, U2.82 (AD1IN_14)
VER_BIT3: R19.2, U2.85 (AD1IN_15)
